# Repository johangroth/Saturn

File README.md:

# Saturn
An SBC based on WDC 65C816.
Will be superseded by Jupiter.

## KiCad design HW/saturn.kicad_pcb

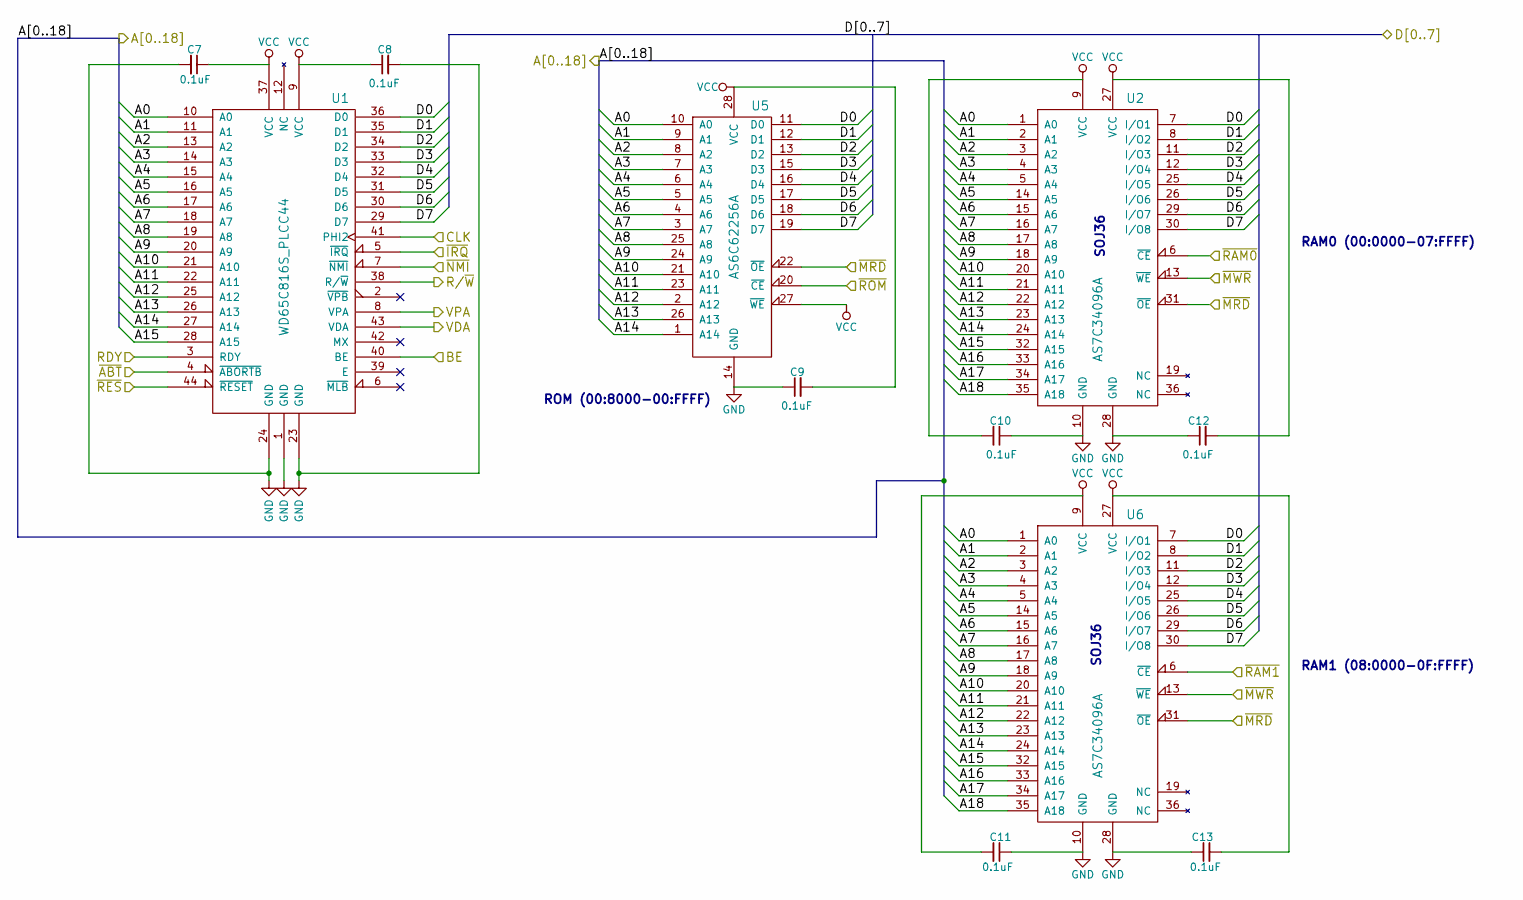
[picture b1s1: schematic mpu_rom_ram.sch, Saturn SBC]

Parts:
C7, C8, C9, C10, C11, C12, C13: 0.1uF; C_Disc_D4.7mm_W2.5mm_P5.00mm
U1: WD65C816S_PLCC44; PLCC-44_THT-Socket
U2, U6: AS7C34096A; SOJ-36
U5: AS6C62256A; DIP-28_W15.24mm_Socket

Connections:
/DUART and line drivers/A0: U1.10 (A0), U2.1 (A0), U5.10 (A0), U6.1 (A0); also elsewhere on the board
/DUART and line drivers/A1: U1.11 (A1), U2.2 (A1), U5.9 (A1), U6.2 (A1); also elsewhere on the board
/DUART and line drivers/A2: U1.13 (A2), U2.3 (A2), U5.8 (A2), U6.3 (A2); also elsewhere on the board
/DUART and line drivers/A3: U1.14 (A3), U2.4 (A3), U5.7 (A3), U6.4 (A3); also elsewhere on the board
/DUART and line drivers/D0: U1.36 (D0), U2.7 (I/O1), U5.11 (D0), U6.7 (I/O1); also elsewhere on the board
/DUART and line drivers/D1: U1.35 (D1), U2.8 (I/O2), U5.12 (D1), U6.8 (I/O2); also elsewhere on the board
/DUART and line drivers/D2: U1.34 (D2), U2.11 (I/O3), U5.13 (D2), U6.11 (I/O3); also elsewhere on the board
/DUART and line drivers/D3: U1.33 (D3), U2.12 (I/O4), U5.15 (D3), U6.12 (I/O4); also elsewhere on the board
/DUART and line drivers/D4: U1.32 (D4), U2.25 (I/O5), U5.16 (D4), U6.25 (I/O5); also elsewhere on the board
/DUART and line drivers/D5: U1.31 (D5), U2.26 (I/O6), U5.17 (D5), U6.26 (I/O6); also elsewhere on the board
/DUART and line drivers/D6: U1.30 (D6), U2.29 (I/O7), U5.18 (D6), U6.29 (I/O7); also elsewhere on the board
/DUART and line drivers/D7: U1.29 (D7), U2.30 (I/O8), U5.19 (D7), U6.30 (I/O8); also elsewhere on the board
/DUART and line drivers/~IRQ: U1.5 (~IRQ); also elsewhere on the board
/DUART and line drivers/~MRD: U2.31 (~OE), U5.22 (~OE), U6.31 (~OE); also elsewhere on the board
/DUART and line drivers/~MWR: U2.13 (~WE), U6.13 (~WE); also elsewhere on the board
/Glue and control logic/A8: U1.19 (A8), U2.17 (A8), U5.25 (A8), U6.17 (A8); also elsewhere on the board
/Glue and control logic/A9: U1.20 (A9), U2.18 (A9), U5.24 (A9), U6.18 (A9); also elsewhere on the board
/Glue and control logic/A10: U1.21 (A10), U2.20 (A10), U5.21 (A10), U6.20 (A10); also elsewhere on the board
/Glue and control logic/A11: U1.22 (A11), U2.21 (A11), U5.23 (A11), U6.21 (A11); also elsewhere on the board
/Glue and control logic/A12: U1.25 (A12), U2.22 (A12), U5.2 (A12), U6.22 (A12); also elsewhere on the board
/Glue and control logic/A13: U1.26 (A13), U2.23 (A13), U5.26 (A13), U6.23 (A13); also elsewhere on the board
/Glue and control logic/A14: U1.27 (A14), U2.24 (A14), U5.1 (A14), U6.24 (A14); also elsewhere on the board
/Glue and control logic/A15: U1.28 (A15), U2.32 (A15), U6.32 (A15); also elsewhere on the board
/Glue and control logic/A16: U2.33 (A16), U6.33 (A16); also elsewhere on the board
/Glue and control logic/A17: U2.34 (A17), U6.34 (A17); also elsewhere on the board
/Glue and control logic/A18: U2.35 (A18), U6.35 (A18); also elsewhere on the board
/Glue and control logic/BE: U1.40 (BE); also elsewhere on the board
/Glue and control logic/CLK: U1.41 (PHI2); also elsewhere on the board
/Glue and control logic/R/~W: U1.38 (R/~W); also elsewhere on the board
/Glue and control logic/RDY: U1.3 (RDY); also elsewhere on the board
/Glue and control logic/VDA: U1.43 (VDA); also elsewhere on the board
/Glue and control logic/VPA: U1.8 (VPA); also elsewhere on the board
/Glue and control logic/~ABT: U1.4 (~ABORTB); also elsewhere on the board
/Glue and control logic/~NMI: U1.7 (~NMI); also elsewhere on the board
/Glue and control logic/~RAM0: U2.6 (~CE); also elsewhere on the board
/Glue and control logic/~RAM1: U6.6 (~CE); also elsewhere on the board
/Glue and control logic/~RES: U1.44 (~RESET); also elsewhere on the board
/Glue and control logic/~ROM: U5.20 (~CE); also elsewhere on the board
/MPU, ROM and RAM/A4: U1.15 (A4), U2.5 (A4), U5.6 (A4), U6.5 (A4); also elsewhere on the board
/MPU, ROM and RAM/A5: U1.16 (A5), U2.14 (A5), U5.5 (A5), U6.14 (A5); also elsewhere on the board
/MPU, ROM and RAM/A6: U1.17 (A6), U2.15 (A6), U5.4 (A6), U6.15 (A6); also elsewhere on the board
/MPU, ROM and RAM/A7: U1.18 (A7), U2.16 (A7), U5.3 (A7), U6.16 (A7); also elsewhere on the board
GND: C7.2, C8.2, C9.1, C10.1, C11.1, C12.1, C13.1, U1.1 (GND), U1.23 (GND), U1.24 (GND), U2.10 (GND), U2.28 (GND), U5.14 (GND), U6.10 (GND), U6.28 (GND); also elsewhere on the board
VCC: C7.1, C8.1, C9.2, C10.2, C11.2, C12.2, C13.2, U1.9 (VCC), U1.37 (VCC), U2.9 (VCC), U2.27 (VCC), U5.27 (~WE), U5.28 (VCC), U6.9 (VCC), U6.27 (VCC); also elsewhere on the board

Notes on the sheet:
SOJ36
RAM0 (00:0000-07:FFFF)
RAM1 (08:0000-0F:FFFF)
ROM (00:8000-00:FFFF)

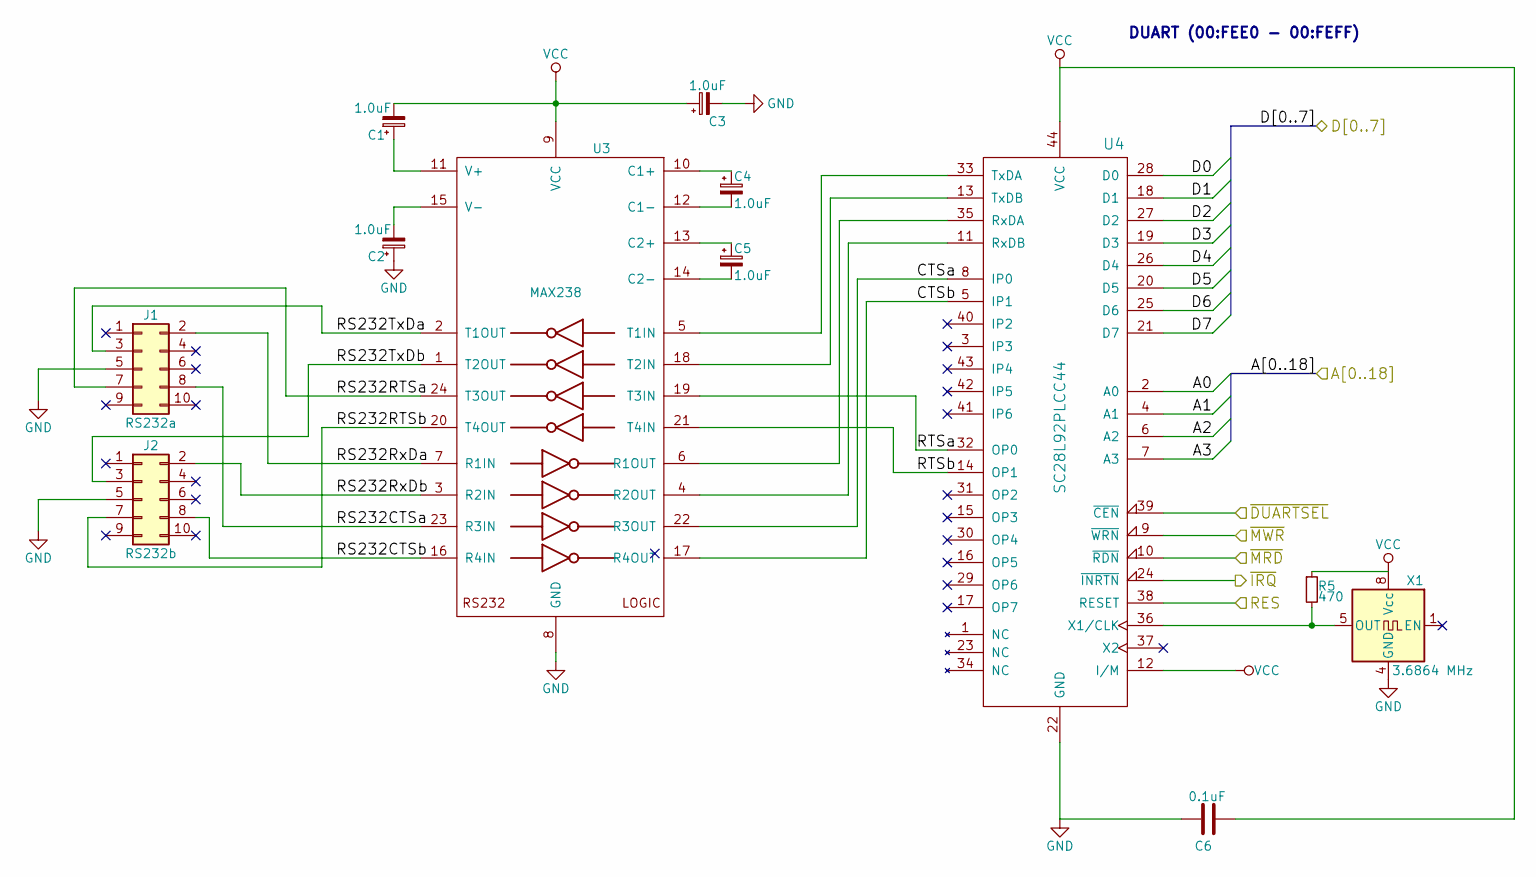
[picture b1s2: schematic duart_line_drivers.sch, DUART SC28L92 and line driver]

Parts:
C1, C2, C3, C4, C5: 1.0uF; CP_Radial_Tantal_D4.5mm_P2.50mm
C6: 0.1uF; C_Disc_D4.7mm_W2.5mm_P5.00mm
J1: RS232a; IDC-Header_2x05_Pitch2.54mm_Straight
J2: RS232b; IDC-Header_2x05_Pitch2.54mm_Straight
R5: 470; R_Axial_DIN0207_L6.3mm_D2.5mm_P2.54mm_Vertical
U3: MAX238; DIP-24_W7.62mm_Socket
U4: SC28L92PLCC44; PLCC-44_THT-Socket
X1: 3.6864 MHz; Oscillator_DIP-8

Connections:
/DUART and line drivers/A0: U4.2 (A0); also elsewhere on the board
/DUART and line drivers/A1: U4.4 (A1); also elsewhere on the board
/DUART and line drivers/A2: U4.6 (A2); also elsewhere on the board
/DUART and line drivers/A3: U4.7 (A3); also elsewhere on the board
/DUART and line drivers/CTSa: U3.22 (R3OUT), U4.8 (IP0)
/DUART and line drivers/CTSb: U3.17 (R4OUT), U4.5 (IP1)
/DUART and line drivers/D0: U4.28 (D0); also elsewhere on the board
/DUART and line drivers/D1: U4.18 (D1); also elsewhere on the board
/DUART and line drivers/D2: U4.27 (D2); also elsewhere on the board
/DUART and line drivers/D3: U4.19 (D3); also elsewhere on the board
/DUART and line drivers/D4: U4.26 (D4); also elsewhere on the board
/DUART and line drivers/D5: U4.20 (D5); also elsewhere on the board
/DUART and line drivers/D6: U4.25 (D6); also elsewhere on the board
/DUART and line drivers/D7: U4.21 (D7); also elsewhere on the board
/DUART and line drivers/RES: U4.38 (RESET); also elsewhere on the board
/DUART and line drivers/RS232CTSa: J1.8, U3.23 (R3IN)
/DUART and line drivers/RS232CTSb: J2.8, U3.16 (R4IN)
/DUART and line drivers/RS232RTSa: J1.7, U3.24 (T3OUT)
/DUART and line drivers/RS232RTSb: J2.7, U3.20 (T4OUT)
/DUART and line drivers/RS232RxDa: J1.2, U3.7 (R1IN)
/DUART and line drivers/RS232RxDb: J2.2, U3.3 (R2IN)
/DUART and line drivers/RS232TxDa: J1.3, U3.2 (T1OUT)
/DUART and line drivers/RS232TxDb: J2.3, U3.1 (T2OUT)
/DUART and line drivers/RTSa: U3.19 (T3IN), U4.32 (OP0)
/DUART and line drivers/RTSb: U3.21 (T4IN), U4.14 (OP1)
/DUART and line drivers/~DUARTSEL: U4.39 (~CEN); also elsewhere on the board
/DUART and line drivers/~IRQ: U4.24 (~INRTN); also elsewhere on the board
/DUART and line drivers/~MRD: U4.10 (~RDN); also elsewhere on the board
/DUART and line drivers/~MWR: U4.9 (~WRN); also elsewhere on the board
GND: C2.1, C3.2, C6.1, J1.5, J2.5, U3.8 (GND), U4.22 (GND), X1.4 (GND); also elsewhere on the board
unnamed: C1.1, U3.11 (V+)
unnamed: C2.2, U3.15 (V-)
unnamed: C4.1, U3.10 (C1+)
unnamed: C4.2, U3.12 (C1-)
unnamed: C5.1, U3.13 (C2+)
unnamed: C5.2, U3.14 (C2-)
unnamed: R5.2, U4.36 (X1/CLK), X1.5 (OUT)
unnamed: U3.4 (R2OUT), U4.11 (RxDB)
unnamed: U3.5 (T1IN), U4.33 (TxDA)
unnamed: U3.6 (R1OUT), U4.35 (RxDA)
unnamed: U3.18 (T2IN), U4.13 (TxDB)
VCC: C1.2, C3.1, C6.2, R5.1, U3.9 (VCC), U4.12 (I/M), U4.44 (VCC), X1.8 (Vcc); also elsewhere on the board

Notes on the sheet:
DUART (00:FEE0 - 00:FEFF)

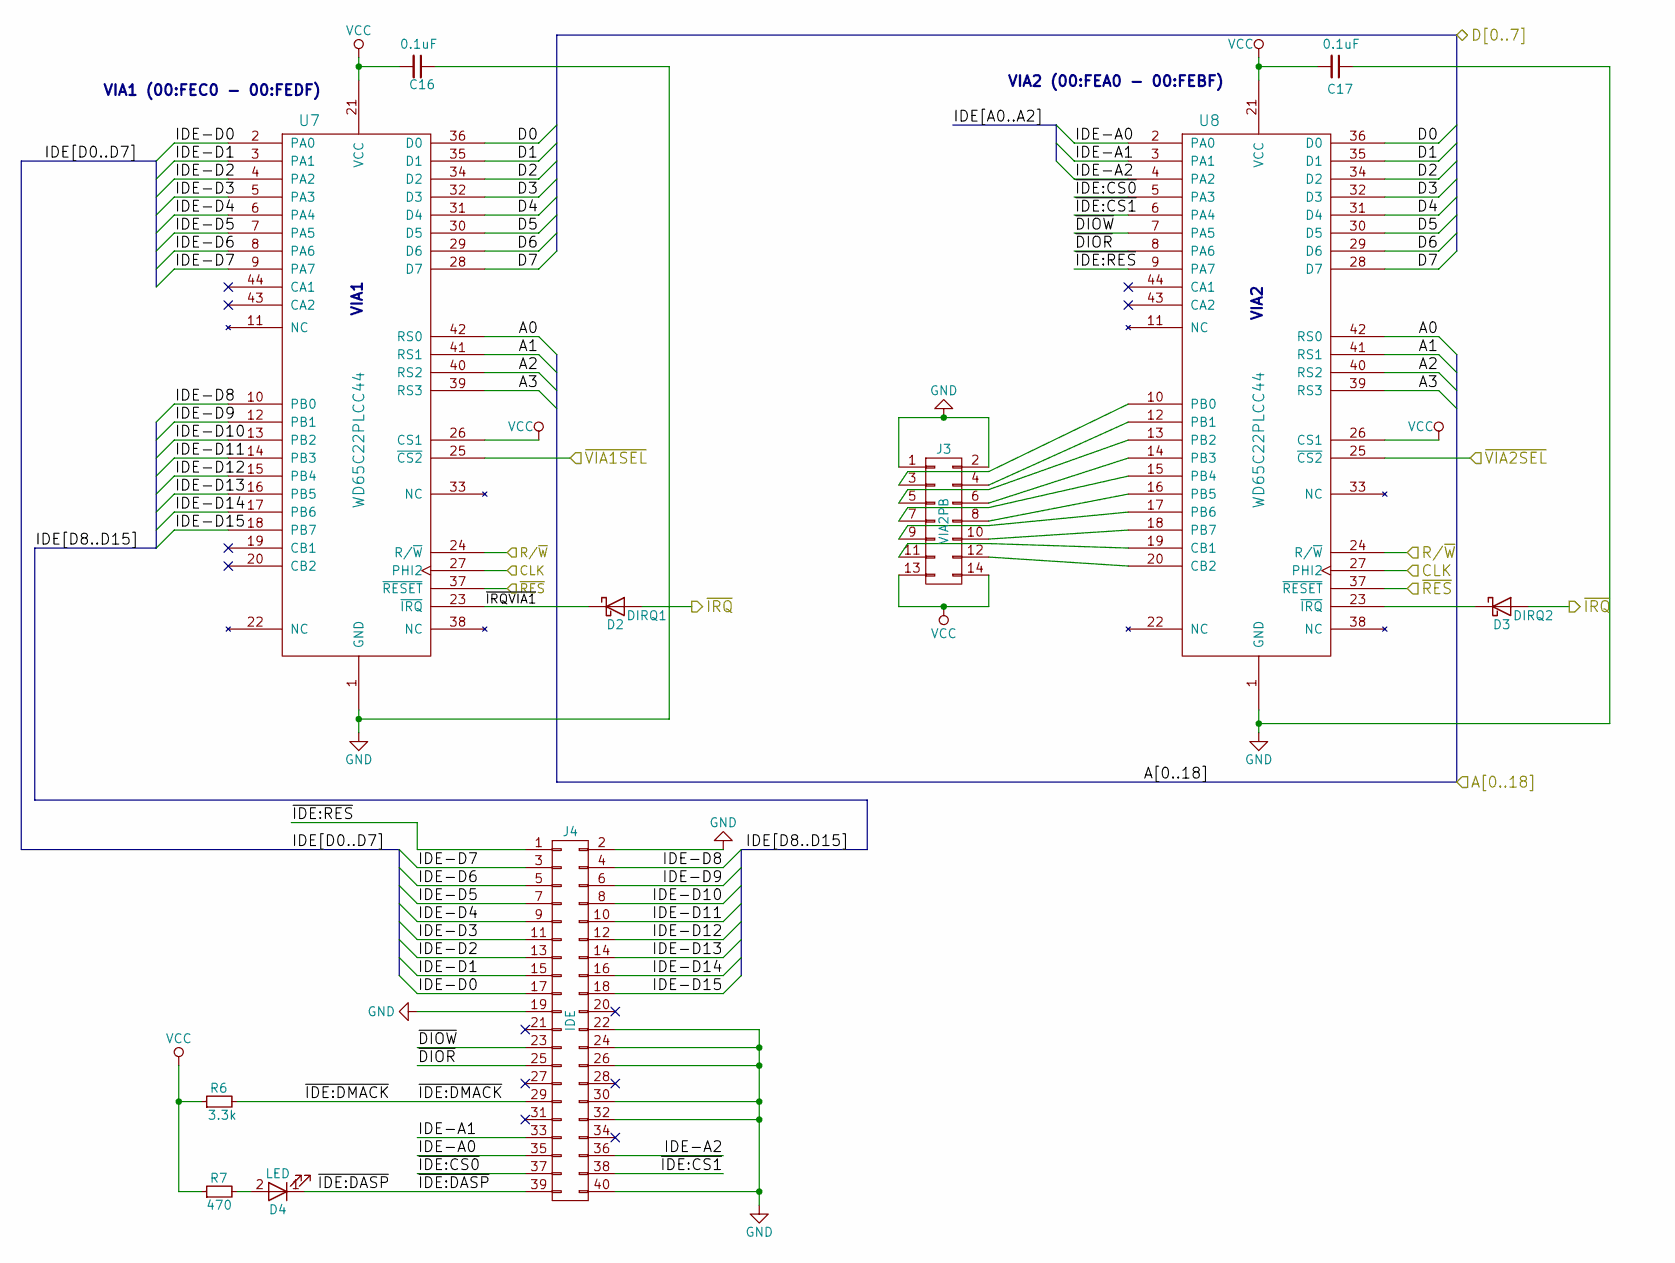
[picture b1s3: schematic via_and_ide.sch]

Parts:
C16, C17: 0.1uF; C_Disc_D4.7mm_W2.5mm_P5.00mm
D2: DIRQ1; D_T-1_P5.08mm_Horizontal
D3: DIRQ2; D_T-1_P5.08mm_Horizontal
D4: LED; LED_D3.0mm
J3: VIA2PB; IDC-Header_2x07_Pitch2.54mm_Straight
J4: IDE; IDC-Header_2x20_Pitch2.54mm_Straight
R6: 3.3k; R_Axial_DIN0207_L6.3mm_D2.5mm_P2.54mm_Vertical
R7: 470; R_Axial_DIN0207_L6.3mm_D2.5mm_P2.54mm_Vertical
U7, U8: WD65C22PLCC44; PLCC-44_THT-Socket

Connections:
/DUART and line drivers/A0: U7.42 (RS0), U8.42 (RS0); also elsewhere on the board
/DUART and line drivers/A1: U7.41 (RS1), U8.41 (RS1); also elsewhere on the board
/DUART and line drivers/A2: U7.40 (RS2), U8.40 (RS2); also elsewhere on the board
/DUART and line drivers/A3: U7.39 (RS3), U8.39 (RS3); also elsewhere on the board
/DUART and line drivers/~IRQ: D2.2 (A), D3.2 (A); also elsewhere on the board
/Glue and control logic/CLK: U7.27 (PHI2), U8.27 (PHI2); also elsewhere on the board
/Glue and control logic/D0: U7.36 (D0), U8.36 (D0); also elsewhere on the board
/Glue and control logic/D1: U7.35 (D1), U8.35 (D1); also elsewhere on the board
/Glue and control logic/D2: U7.34 (D2), U8.34 (D2); also elsewhere on the board
/Glue and control logic/D3: U7.32 (D3), U8.32 (D3); also elsewhere on the board
/Glue and control logic/R/~W: U7.24 (R/~W), U8.24 (R/~W); also elsewhere on the board
/Glue and control logic/~RES: U7.37 (~RESET), U8.37 (~RESET); also elsewhere on the board
/Glue and control logic/~VIA1SEL: U7.25 (~CS2); also elsewhere on the board
/Glue and control logic/~VIA2SEL: U8.25 (~CS2); also elsewhere on the board
/VIA and IDE/D4: U7.31 (D4), U8.31 (D4)
/VIA and IDE/D5: U7.30 (D5), U8.30 (D5)
/VIA and IDE/D6: U7.29 (D6), U8.29 (D6)
/VIA and IDE/D7: U7.28 (D7), U8.28 (D7)
/VIA and IDE/IDE-A0: J4.35, U8.2 (PA0)
/VIA and IDE/IDE-A1: J4.33, U8.3 (PA1)
/VIA and IDE/IDE-A2: J4.36, U8.4 (PA2)
/VIA and IDE/IDE-D0: J4.17, U7.2 (PA0)
/VIA and IDE/IDE-D1: J4.15, U7.3 (PA1)
/VIA and IDE/IDE-D2: J4.13, U7.4 (PA2)
/VIA and IDE/IDE-D3: J4.11, U7.5 (PA3)
/VIA and IDE/IDE-D4: J4.9, U7.6 (PA4)
/VIA and IDE/IDE-D5: J4.7, U7.7 (PA5)
/VIA and IDE/IDE-D6: J4.5, U7.8 (PA6)
/VIA and IDE/IDE-D7: J4.3, U7.9 (PA7)
/VIA and IDE/IDE-D8: J4.4, U7.10 (PB0)
/VIA and IDE/IDE-D9: J4.6, U7.12 (PB1)
/VIA and IDE/IDE-D10: J4.8, U7.13 (PB2)
/VIA and IDE/IDE-D11: J4.10, U7.14 (PB3)
/VIA and IDE/IDE-D12: J4.12, U7.15 (PB4)
/VIA and IDE/IDE-D13: J4.14, U7.16 (PB5)
/VIA and IDE/IDE-D14: J4.16, U7.17 (PB6)
/VIA and IDE/IDE-D15: J4.18, U7.18 (PB7)
/VIA and IDE/~DIOR: J4.25, U8.8 (PA6)
/VIA and IDE/~DIOW: J4.23, U8.7 (PA5)
/VIA and IDE/~IDE:CS0: J4.37, U8.5 (PA3)
/VIA and IDE/~IDE:CS1: J4.38, U8.6 (PA4)
/VIA and IDE/~IDE:DASP: D4.1 (K), J4.39
/VIA and IDE/~IDE:DMACK: J4.29, R6.2
/VIA and IDE/~IDE:RES: J4.1, U8.9 (PA7)
/VIA and IDE/~IRQVIA1: D2.1 (K), U7.23 (~IRQ)
GND: C16.1, C17.1, J3.1, J3.2, J4.2, J4.19, J4.22, J4.24, J4.26, J4.30, J4.32, J4.40, U7.1 (GND), U8.1 (GND); also elsewhere on the board
unnamed: D3.1 (K), U8.23 (~IRQ)
unnamed: D4.2 (A), R7.2
unnamed: J3.3, U8.10 (PB0)
unnamed: J3.4, U8.12 (PB1)
unnamed: J3.5, U8.13 (PB2)
unnamed: J3.6, U8.14 (PB3)
unnamed: J3.7, U8.15 (PB4)
unnamed: J3.8, U8.16 (PB5)
unnamed: J3.9, U8.17 (PB6)
unnamed: J3.10, U8.18 (PB7)
unnamed: J3.11, U8.19 (CB1)
unnamed: J3.12, U8.20 (CB2)
VCC: C16.2, C17.2, J3.13, J3.14, R6.1, R7.1, U7.21 (VCC), U7.26 (CS1), U8.21 (VCC), U8.26 (CS1); also elsewhere on the board

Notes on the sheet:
VIA2
VIA1
VIA1 (00:FEC0 - 00:FEDF)
VIA2 (00:FEA0 - 00:FEBF)

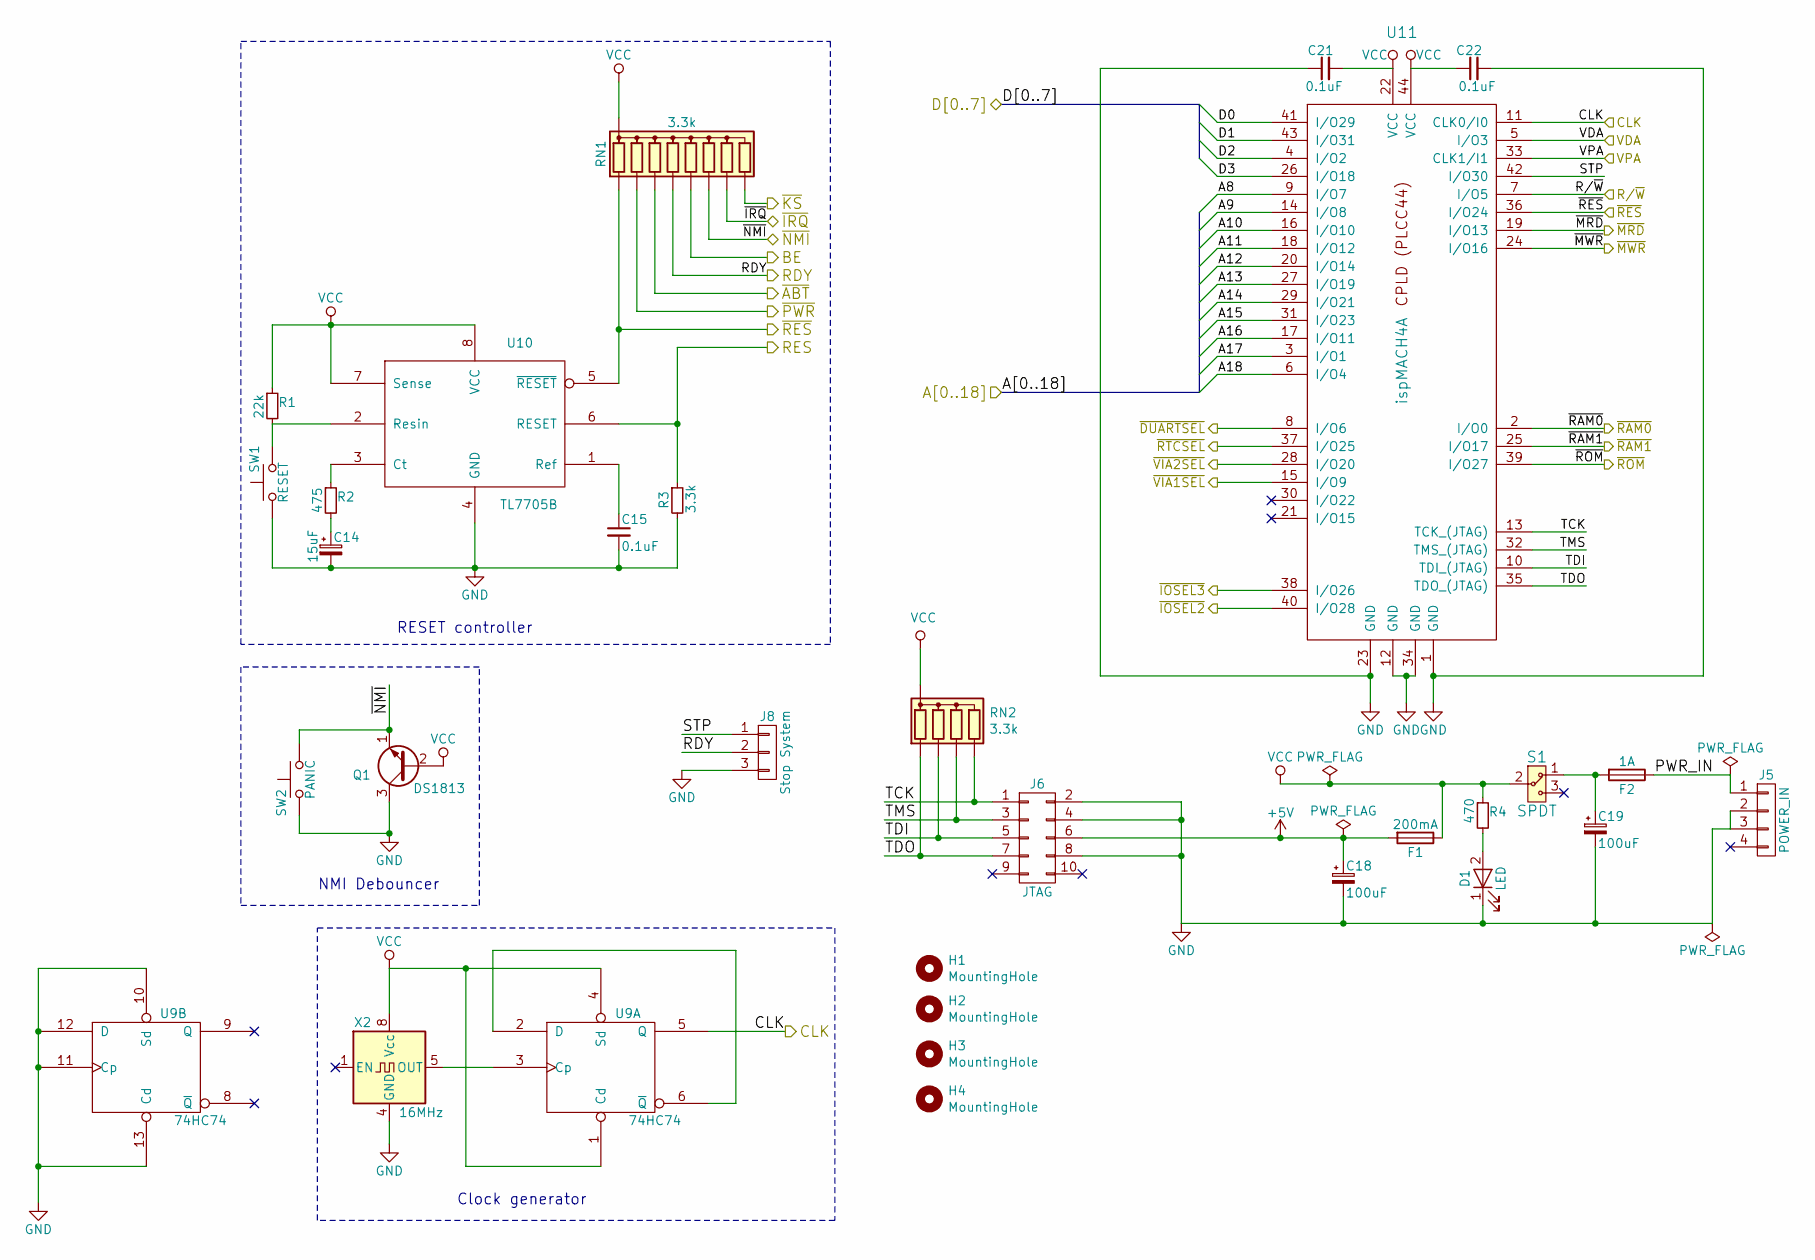
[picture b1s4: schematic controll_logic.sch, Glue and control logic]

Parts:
C14: 15uF; CP_Radial_D5.0mm_P2.50mm
C15, C21, C22: 0.1uF; C_Disc_D4.7mm_W2.5mm_P5.00mm
C18, C19: 100uF; CP_Radial_D6.3mm_P2.50mm
D1: LED; LED_D3.0mm
F1: 200mA; Fuseholder5x20_horiz_open_Schurter_0031_8201
F2: 1A; Fuseholder5x20_horiz_open_Schurter_0031_8201
H1, H2, H3, H4: MountingHole; MountingHole_3.2mm_M3_DIN965_Pad
J5: POWER_IN; Molex_NanoFit_1x04x2.50mm_Angled
J6: JTAG; IDC-Header_2x05_Pitch2.54mm_Straight
J8: Stop System; Pin_Header_Straight_1x03_Pitch2.54mm
Q1: DS1813; TO-92_Inline_Narrow_Oval
R1: 22k; R_Axial_DIN0207_L6.3mm_D2.5mm_P2.54mm_Vertical
R2: 475; R_Axial_DIN0207_L6.3mm_D2.5mm_P2.54mm_Vertical
R3: 3.3k; R_Axial_DIN0207_L6.3mm_D2.5mm_P2.54mm_Vertical
R4: 470; R_Axial_DIN0207_L6.3mm_D2.5mm_P2.54mm_Vertical
RN1: 3.3k; R_Array_SIP9
RN2: 3.3k; R_Array_SIP5
S1: SPDT; SW-SPDT-0900766b81587629
SW1: RESET; SW_PUSH_6mm_h4.3mm
SW2: PANIC; SW_PUSH_6mm_h4.3mm
U9: 74HC74; DIP-14_W7.62mm_Socket
U10: TL7705B; DIP-8_W7.62mm_Socket
U11: ispMACH4A; PLCC-44_THT-Socket
X2: 16MHz; Oscillator_DIP-8

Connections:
+5V: C18.1, F1.2, J6.6
/DUART and line drivers/RES: R3.1, U10.6 (RESET); also elsewhere on the board
/DUART and line drivers/~DUARTSEL: U11.8 (I/O6); also elsewhere on the board
/DUART and line drivers/~IRQ: RN1.8 (R7); also elsewhere on the board
/DUART and line drivers/~MRD: U11.19 (I/O13); also elsewhere on the board
/DUART and line drivers/~MWR: U11.24 (I/O16); also elsewhere on the board
/Glue and control logic/A8: U11.9 (I/O7); also elsewhere on the board
/Glue and control logic/A9: U11.14 (I/O8); also elsewhere on the board
/Glue and control logic/A10: U11.16 (I/O10); also elsewhere on the board
/Glue and control logic/A11: U11.18 (I/O12); also elsewhere on the board
/Glue and control logic/A12: U11.20 (I/O14); also elsewhere on the board
/Glue and control logic/A13: U11.27 (I/O19); also elsewhere on the board
/Glue and control logic/A14: U11.29 (I/O21); also elsewhere on the board
/Glue and control logic/A15: U11.31 (I/O23); also elsewhere on the board
/Glue and control logic/A16: U11.17 (I/O11); also elsewhere on the board
/Glue and control logic/A17: U11.3 (I/O1); also elsewhere on the board
/Glue and control logic/A18: U11.6 (I/O4); also elsewhere on the board
/Glue and control logic/BE: RN1.6 (R5); also elsewhere on the board
/Glue and control logic/CLK: U9.5 (Q), U11.11 (CLK0/I0); also elsewhere on the board
/Glue and control logic/D0: U11.41 (I/O29); also elsewhere on the board
/Glue and control logic/D1: U11.43 (I/O31); also elsewhere on the board
/Glue and control logic/D2: U11.4 (I/O2); also elsewhere on the board
/Glue and control logic/D3: U11.26 (I/O18); also elsewhere on the board
/Glue and control logic/PWR_IN: F2.1, J5.1
/Glue and control logic/R/~W: U11.7 (I/O5); also elsewhere on the board
/Glue and control logic/RDY: J8.2, RN1.5 (R4); also elsewhere on the board
/Glue and control logic/STP: J8.1, U11.42 (I/O30)
/Glue and control logic/TCK: J6.1, RN2.5 (R4), U11.13 (TCK_(JTAG))
/Glue and control logic/TDI: J6.5, RN2.3 (R2), U11.10 (TDI_(JTAG))
/Glue and control logic/TDO: J6.7, RN2.2 (R1), U11.35 (TDO_(JTAG))
/Glue and control logic/TMS: J6.3, RN2.4 (R3), U11.32 (TMS_(JTAG))
/Glue and control logic/VDA: U11.5 (I/O3); also elsewhere on the board
/Glue and control logic/VPA: U11.33 (CLK1/I1); also elsewhere on the board
/Glue and control logic/~ABT: RN1.4 (R3); also elsewhere on the board
/Glue and control logic/~IOSEL2: U11.40 (I/O28); also elsewhere on the board
/Glue and control logic/~IOSEL3: U11.38 (I/O26); also elsewhere on the board
/Glue and control logic/~KS: RN1.9 (R8); also elsewhere on the board
/Glue and control logic/~NMI: Q1.1 (E), RN1.7 (R6), SW2.1; also elsewhere on the board
/Glue and control logic/~PWR: RN1.3 (R2); also elsewhere on the board
/Glue and control logic/~RAM0: U11.2 (I/O0); also elsewhere on the board
/Glue and control logic/~RAM1: U11.25 (I/O17); also elsewhere on the board
/Glue and control logic/~RES: RN1.2 (R1), U10.5 (~RESET), U11.36 (I/O24); also elsewhere on the board
/Glue and control logic/~ROM: U11.39 (I/O27); also elsewhere on the board
/Glue and control logic/~RTCSEL: U11.37 (I/O25); also elsewhere on the board
/Glue and control logic/~VIA1SEL: U11.15 (I/O9); also elsewhere on the board
/Glue and control logic/~VIA2SEL: U11.28 (I/O20); also elsewhere on the board
GND: C14.2, C15.2, C18.2, C19.2, C21.1, C22.2, D1.1 (K), J5.2, J5.3, J6.2, J6.4, J6.8, J8.3, Q1.3 (C), R3.2, SW1.1, SW2.2, U9.7 (GND), U9.10 (Sd), U9.11 (Cp), U9.12 (D), U9.13 (Cd), U10.4 (GND), U11.1 (GND), U11.12 (GND), U11.23 (GND), U11.34 (GND), X2.4 (GND); also elsewhere on the board
unnamed: C14.1, R2.2
unnamed: C15.1, U10.1 (Ref)
unnamed: C19.1, F2.2, S1.1
unnamed: D1.2 (A), R4.2
unnamed: R1.2, SW1.2, U10.2 (Resin)
unnamed: R2.1, U10.3 (Ct)
unnamed: U9.2 (D), U9.6 (~Q)
unnamed: U9.3 (Cp), X2.5 (OUT)
VCC: C21.2, C22.1, F1.1, Q1.2 (B), R1.1, R4.1, RN1.1 (common), RN2.1 (common), S1.2 (COM), U9.1 (Cd), U9.4 (Sd), U9.14 (VCC), U10.7 (Sense), U10.8 (VCC), U11.22 (VCC), U11.44 (VCC), X2.8 (Vcc); also elsewhere on the board

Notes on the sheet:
RESET controller
Clock generator
NMI Debouncer

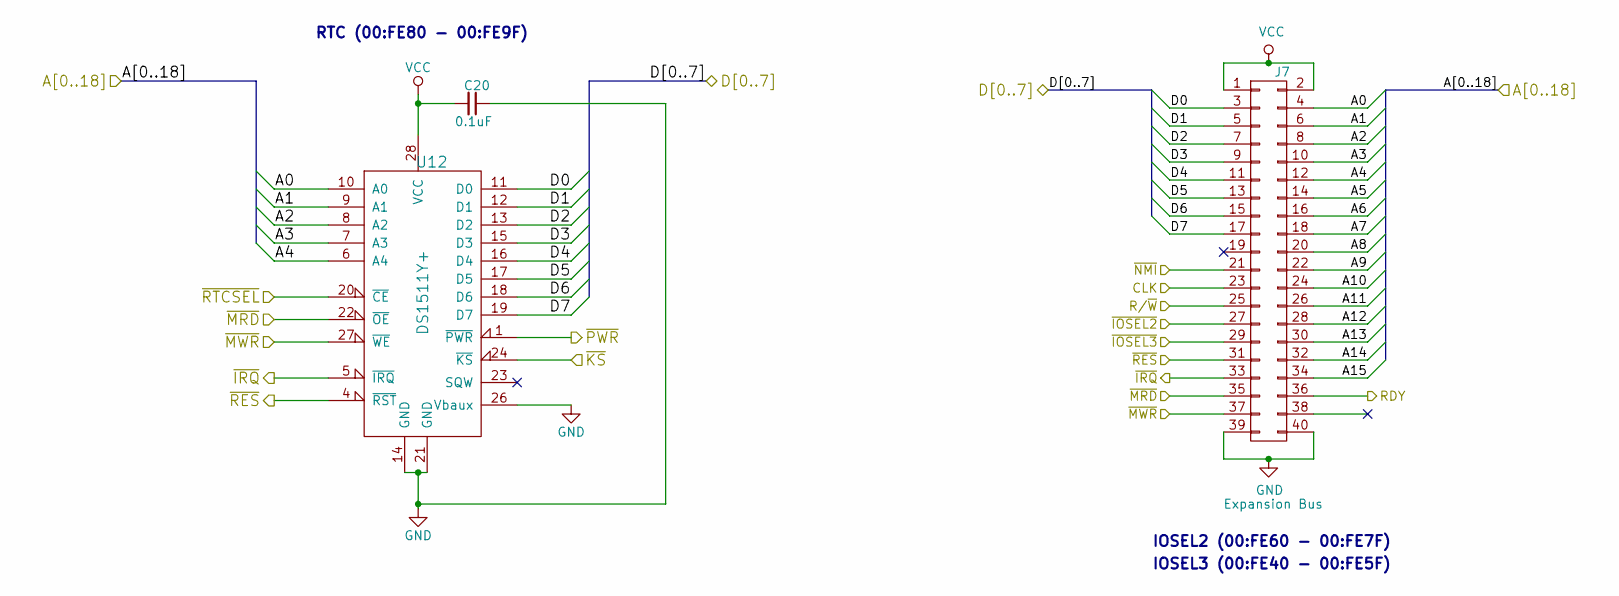
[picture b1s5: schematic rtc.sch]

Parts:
C20: 0.1uF; C_Disc_D4.7mm_W2.5mm_P5.00mm
J7: Expansion Bus; IDC-Header_2x20_Pitch2.54mm_Straight
U12: DS1511Y+; DIP-28_W15.24mm_Socket

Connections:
/DUART and line drivers/A0: J7.4, U12.10 (A0); also elsewhere on the board
/DUART and line drivers/A1: J7.6, U12.9 (A1); also elsewhere on the board
/DUART and line drivers/A2: J7.8, U12.8 (A2); also elsewhere on the board
/DUART and line drivers/A3: J7.10, U12.7 (A3); also elsewhere on the board
/DUART and line drivers/D0: J7.3, U12.11 (D0); also elsewhere on the board
/DUART and line drivers/D1: J7.5, U12.12 (D1); also elsewhere on the board
/DUART and line drivers/D2: J7.7, U12.13 (D2); also elsewhere on the board
/DUART and line drivers/D3: J7.9, U12.15 (D3); also elsewhere on the board
/DUART and line drivers/D4: J7.11, U12.16 (D4); also elsewhere on the board
/DUART and line drivers/D5: J7.13, U12.17 (D5); also elsewhere on the board
/DUART and line drivers/D6: J7.15, U12.18 (D6); also elsewhere on the board
/DUART and line drivers/D7: J7.17, U12.19 (D7); also elsewhere on the board
/DUART and line drivers/~IRQ: J7.33, U12.5 (~IRQ); also elsewhere on the board
/DUART and line drivers/~MRD: J7.35, U12.22 (~OE); also elsewhere on the board
/DUART and line drivers/~MWR: J7.37, U12.27 (~WE); also elsewhere on the board
/Glue and control logic/A8: J7.20; also elsewhere on the board
/Glue and control logic/A9: J7.22; also elsewhere on the board
/Glue and control logic/A10: J7.24; also elsewhere on the board
/Glue and control logic/A11: J7.26; also elsewhere on the board
/Glue and control logic/A12: J7.28; also elsewhere on the board
/Glue and control logic/A13: J7.30; also elsewhere on the board
/Glue and control logic/A14: J7.32; also elsewhere on the board
/Glue and control logic/A15: J7.34; also elsewhere on the board
/Glue and control logic/CLK: J7.23; also elsewhere on the board
/Glue and control logic/R/~W: J7.25; also elsewhere on the board
/Glue and control logic/RDY: J7.36; also elsewhere on the board
/Glue and control logic/~IOSEL2: J7.27; also elsewhere on the board
/Glue and control logic/~IOSEL3: J7.29; also elsewhere on the board
/Glue and control logic/~KS: U12.24 (~KS); also elsewhere on the board
/Glue and control logic/~NMI: J7.21; also elsewhere on the board
/Glue and control logic/~PWR: U12.1 (~PWR); also elsewhere on the board
/Glue and control logic/~RES: J7.31, U12.4 (~RST); also elsewhere on the board
/Glue and control logic/~RTCSEL: U12.20 (~CE); also elsewhere on the board
/MPU, ROM and RAM/A4: J7.12, U12.6 (A4); also elsewhere on the board
/MPU, ROM and RAM/A5: J7.14; also elsewhere on the board
/MPU, ROM and RAM/A6: J7.16; also elsewhere on the board
/MPU, ROM and RAM/A7: J7.18; also elsewhere on the board
GND: C20.1, J7.39, J7.40, U12.14 (GND), U12.21 (GND), U12.26 (Vbaux); also elsewhere on the board
VCC: C20.2, J7.1, J7.2, U12.28 (VCC); also elsewhere on the board

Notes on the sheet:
RTC (00:FE80 - 00:FE9F)
IOSEL2 (00:FE60 - 00:FE7F)
IOSEL3 (00:FE40 - 00:FE5F)

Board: 4 copper layers, 67 parts (0 on the bottom side), 138 nets, no tracks yet.

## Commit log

2017-07-10 First commit.
2017-07-10 Filename changes.
2017-12-22 Added ram, vias, rtc and ide connector. Managed to delete Pluto's CPLD schemas.
2017-12-23 Address, databus and control signals added to RAM and ROM
2017-12-23 Moved CPLD logic to root directory.
2017-12-23 Renamed SaturnPOC to CPLD.
2017-12-23 Finished RAM/ROM/CPU control signals.
2017-12-25 Small changes.
2017-12-26 Added address decoding.
2018-01-05 Simulation of address decoding.
2018-03-29 ABEL code passes compilation, no tests though. Small changes to schema
2018-03-29 Added datasheets for SC16C2550B (quart 64B FIFO), ATF1504 and ST16C550 (uart).
2018-06-20 Added BDD CPLD code 0.5.1
2018-06-20 renamed bdd cupld file.
2019-03-25 Removed two ram chips, down to 1 MiB.
2019-06-09 Added new footprints. Added docs
2019-06-09 Rescue lib added after upgrade to 5.1
2019-06-09 Fixed bus error in RTC design.
2019-06-23 Cosmetic changes to schema. Parking this project as router can't find a route.
2019-07-07 Some schematics updates
